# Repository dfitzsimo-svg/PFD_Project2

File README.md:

# PFD_Project2

In this proam trying to make a 737 style standby PFD that can show real time speed, altitude, and attitude.
I am using an ESP32 along with a GPS module, barometer and IMU to measure the kinematics. A list of all my components is giving in the project files along with some notes on each. I started the project by first writing Python code in Virtual Studio to simulate the look of the real life 737 max standby horizon as much as possible. I started out using Python and a virtual screen at first as I was much more familiar with that language and being able to use a virtual screen meant I could quickly make edits, see how it looked and then move on without having to flash the code to a physical device each time.

After I was happy with how everything looked, I translated my code over to the Arduino IDE in order to flash it to my ESP. This is where I encountered a few problems and had to make large adjustments to my code. The biggest problem was the low amount of memory of the ESP. At only -500 Kb, I had a small budget of memory and had to try many optimisation techniques. The most beneficial of these was to create sprites for certain elements of the graphics and to seperate the screen into chunks depending on their required refresh rates.

Once I had sorted the graphical issues, I then moved on to incorporating all my sensors together onto a breadboard. This turned out to be very straightforward as I had done plenty of testing with my Python code with fake sensor data. The only issue I had here was from poor connection quality from the breadboard. The next addition was to power the device with a battery as it would be in my final version. This is something that turned out harder than I expected but forced me to learn a lot about battery tech, power regulation and general circuit design. I ended up using a simple 1S LiPo with a TP4056 for charge protection and an MT3608 for voltage regulation to maintain 5V supply to the ESP.

After I was happy with the breadboard prototype, I began by designing my PCB using KiCAD which I was new to but found it to be extremely intuitive and easy to learn. At this stage I have fully completed my schematic and am now trying to settle on a board layout for all the modules. 

## Hardware used

- Elegoo ESP32
- ILI9488 3.5" SPI screen, 480x320
- NEO-6M GPS - speed
- BMP280 - altitude (want to add a rotary encoder for QNH later)
- MPU6050 - pitch/roll

## Sidenotes
I originally began by using a Raspberry Pi that I had laying around but the pi lacked the RAM to push detailed graphics to the screen via SPI and also lacked a ready to use driver. This is a known limitation of the chip itself, not something specific to the Pi. I had to write my own driver since there was no existing Linux library that handled this properly. Even after that, the performance was poor and the frame rate was slow.

Change from Pi to ESP:

- Same layout/logic as the Python version, ported to C++
- Drawing straight to the screen caused bad flicker
- Tried a full-screen buffer to fix it but ran out of contiguous RAM
- Fixed it by drawing in 4 horizontal bands instead, each with its own small buffer

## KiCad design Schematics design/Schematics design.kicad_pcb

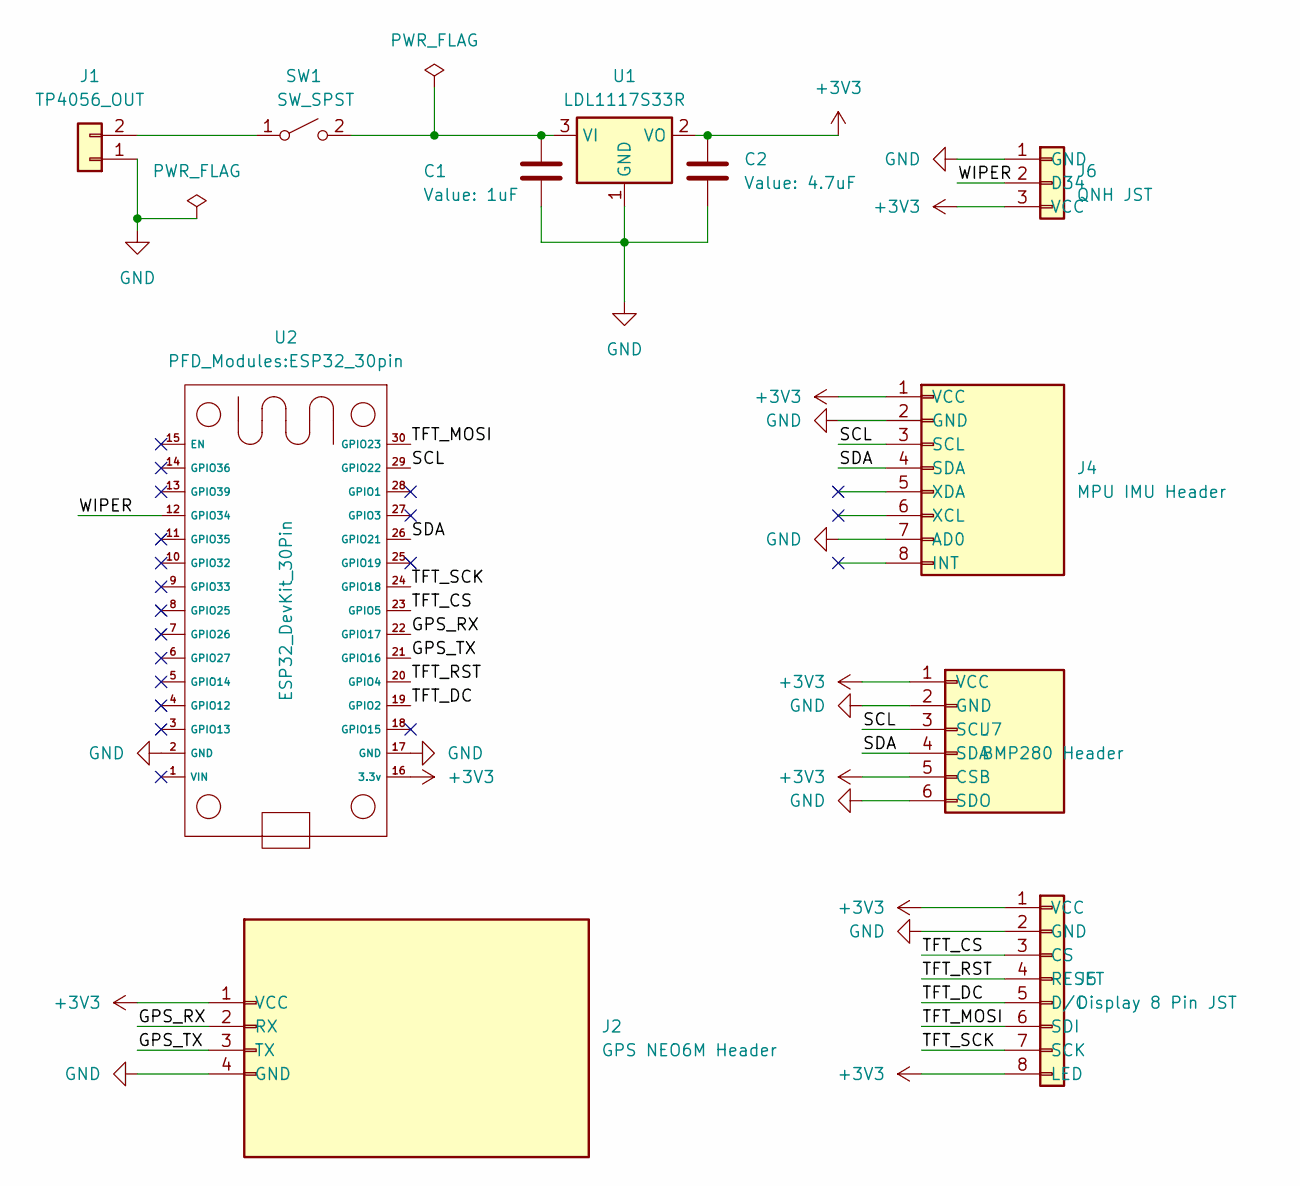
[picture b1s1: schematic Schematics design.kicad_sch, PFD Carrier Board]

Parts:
C1: 1uF; C_0805_2012Metric_Pad1.18x1.45mm_HandSolder
C2: 4.7uF; C_0805_2012Metric_Pad1.18x1.45mm_HandSolder
J1: TP4056_OUT; JST_PH_B2B-PH-K_1x02_P2.00mm_Vertical
J2: GPS NEO6M Header; PinHeader_1x04_P2.54mm_Vertical
J4: MPU IMU Header; PinHeader_1x08_P2.54mm_Vertical
J5: Display 8 Pin JST; JST_PH_B8B-PH-K_1x08_P2.00mm_Vertical
J6: QNH JST; JST_PH_B3B-PH-K_1x03_P2.00mm_Vertical
J7: BMP280 Header; PinHeader_1x06_P2.54mm_Vertical
SW1: SW_SPST; JST_PH_B2B-PH-K_1x02_P2.00mm_Vertical
U1: LDL1117S33R; SOT-223-3_TabPin2
U2: ESP32_DevKit_30Pin; ESP32_30pin

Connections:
+3V3: C2.2, J2.1 (VCC), J4.1 (VCC), J5.1 (VCC), J5.8 (LED), J6.3 (VCC), J7.1 (VCC), J7.5 (CSB), U1.2 (VO), U2.16 (3.3v)
/GPS_RX: J2.2 (RX), U2.22 (GPIO17)
/GPS_TX: J2.3 (TX), U2.21 (GPIO16)
/SCL: J4.3 (SCL), J7.3 (SCL), U2.29 (GPIO22)
/SDA: J4.4 (SDA), J7.4 (SDA), U2.26 (GPIO21)
/TFT_CS: J5.3 (CS), U2.23 (GPIO5)
/TFT_DC: J5.5 (D/C), U2.19 (GPIO2)
/TFT_MOSI: J5.6 (SDI), U2.30 (GPIO23)
/TFT_RST: J5.4 (RESET), U2.20 (GPIO4)
/TFT_SCK: J5.7 (SCK), U2.24 (GPIO18)
/WIPER: J6.2 (D34), U2.12 (GPIO34)
GND: C1.1, C2.1, J1.1, J2.4 (GND), J4.2 (GND), J4.7 (AD0), J5.2 (GND), J6.1 (GND), J7.2 (GND), J7.6 (SDO), U1.1 (GND), U2.2 (GND), U2.17 (GND); also elsewhere on the board
unnamed 12: J1.2, SW1.1 (A); also elsewhere on the board
unnamed: C1.2, SW1.2 (B), U1.3 (VI)

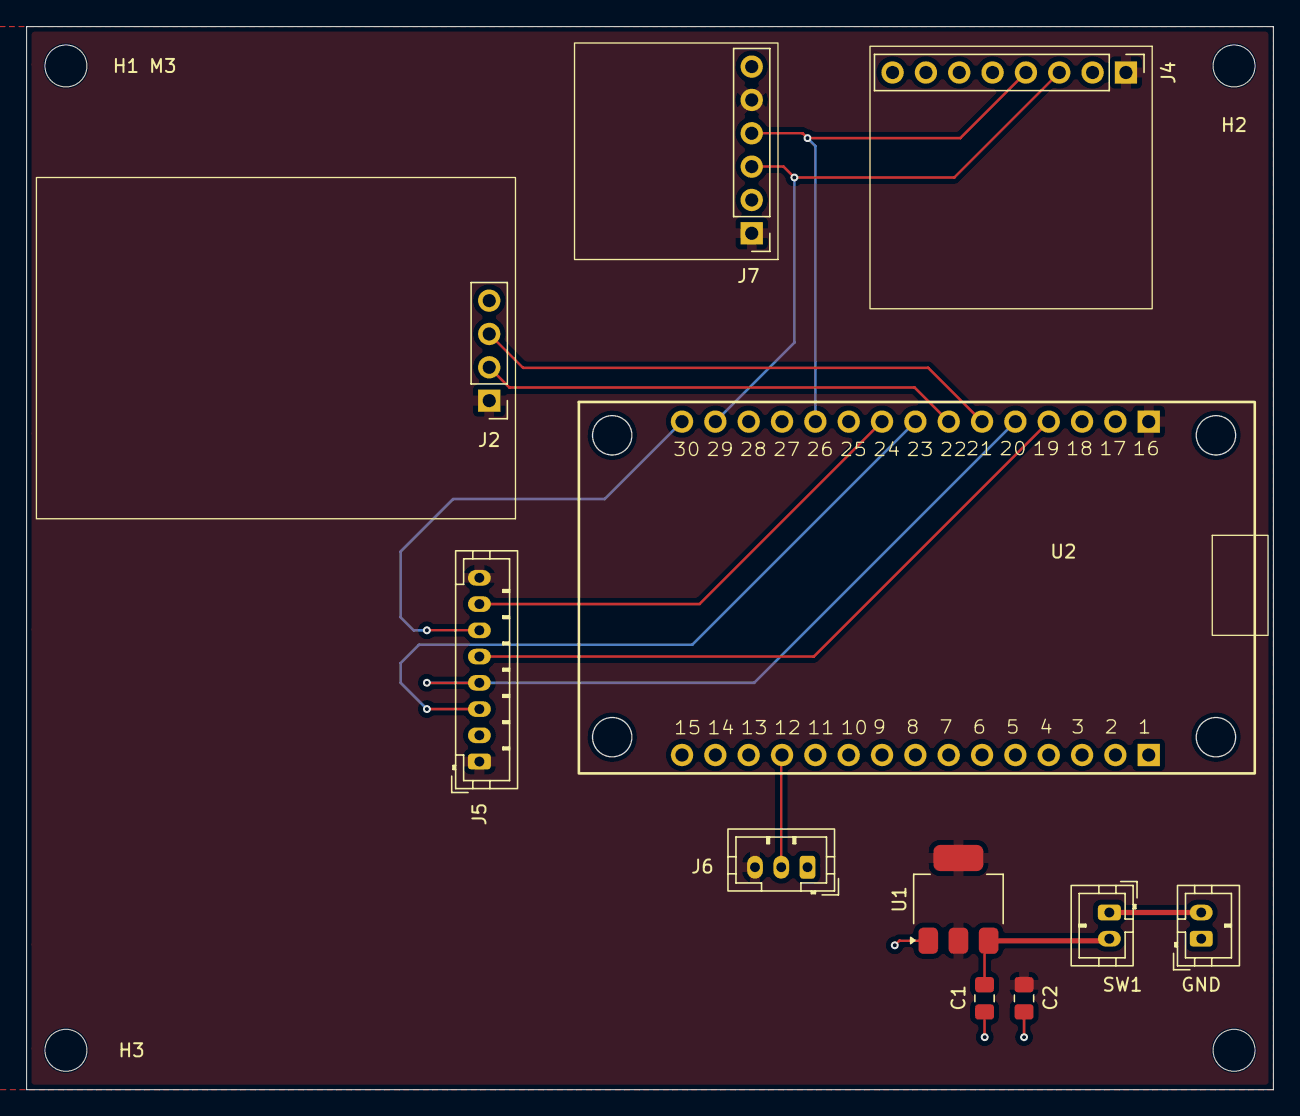
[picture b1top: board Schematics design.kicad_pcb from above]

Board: 2 copper layers, 95.0 x 81.0 mm, 14 parts (0 on the bottom side), 14 nets.

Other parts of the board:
GND: TP4056_OUT; JST_PH_B2B-PH-K_1x02_P2.00mm_Vertical
H1 M3, H3: MountingHole_3.2mm_M3
H2: M3; MountingHole_3.2mm_M3

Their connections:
GND: GND.1; also elsewhere on the board
unnamed 12: GND.2; also elsewhere on the board

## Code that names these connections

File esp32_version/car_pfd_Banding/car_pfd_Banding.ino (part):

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float seaLevelhPa = 1013.25; //hPa - now set by the QNH pot (see readQnhPot)

// ---- QNH potentiometer ----
// 10k linear pot: outer pins to 3V3 and GND, middle (wiper) to GPIO34.
const int   QNH_POT_PIN = 34;
const float QNH_MIN = 950.0;      // hPa at one end of the pot
const float QNH_MAX = 1050.0;     // hPa at the other end
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const unsigned long IMU_READ_INTERVAL_MS = 20;

TinyGPSPlus gps;
HardwareSerial gpsSerial(2);  // UART2 - GPIO16 RX, GPIO17 TX

// Track whether we've ever had a valid fix. Once true, we start
// showing GPS speed instead of the ramp. If the fix is later lost,
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
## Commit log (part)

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2026-04-05 Initial working version
2026-04-05 Add ignore rules and stop tracking generated files
2026-04-05 Add requirements.txt
